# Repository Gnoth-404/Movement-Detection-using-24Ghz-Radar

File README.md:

# Movement-Detection-using-24Ghz-Radar
Adaptive movement detection using 24Ghz Radar and CFAR Algorithm

# Radar Movement Detection System

## Project Overview
This project implemented a radar-based movement detection system using  IPM165 radar sensor, FreeSoc2 Development Board, along with CA-CFAR algorithm. The system included custom PCB design, radar signal processing, and 3D-printed enclosure.

## Features
- 4-layer PCB design integrating IPM165 radar sensor
- Two-stage bandpass filter with gain of 300
- DMA streaming from ADC to Memory
- Signal processing using Hanning window and FFT
- Movement detection using CA-CFAR algorithm
- Custom 3D-printed enclosure

## Hardware
### PCB Design
- 4-layer PCB designed in Kicad
- Integrates IPM165 radar sensor
- Includes two-stage bandpass filter (Gain = 300)

### Enclosure
- Custom 3D-printed designed in Onshape

## Software
### Firmware (C)
- DMA streaming from ADC
- Hanning window application
- FFT implementation
- CA-CFAR algorithm for movement detection

### MATLAB
- Verification script for signal processing algorithms

## Results and Performance

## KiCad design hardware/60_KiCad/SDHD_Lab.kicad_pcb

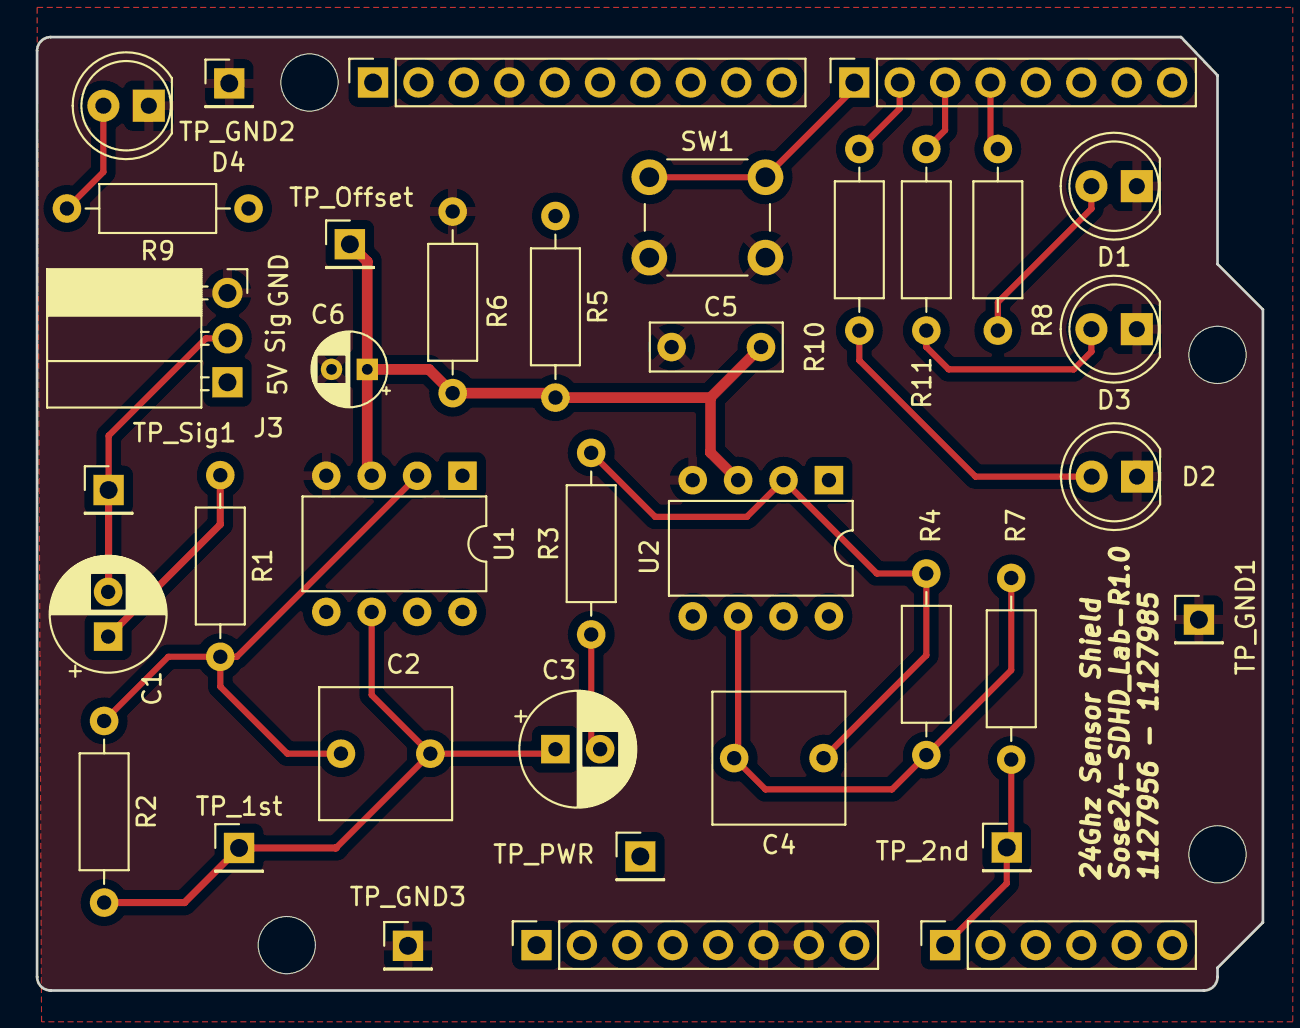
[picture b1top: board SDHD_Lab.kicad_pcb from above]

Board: 4 copper layers, 68.6 x 53.3 mm, 41 parts (0 on the bottom side), 19 nets.

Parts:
C1, C3: 4.7u; CP_Radial_D6.3mm_P2.50mm
C2: 1.5n; C_Rect_L7.2mm_W7.2mm_P5.00mm_FKS2_FKP2_MKS2_MKP2
C4: 3.3n; C_Rect_L7.2mm_W7.2mm_P5.00mm_FKS2_FKP2_MKS2_MKP2
C5: 100n; C_Rect_L7.2mm_W2.5mm_P5.00mm_FKS2_FKP2_MKS2_MKP2
C6: 22u; CP_Radial_D4.0mm_P2.00mm
D1: Red_LED; LED_D5.0mm
D2: Green_LED; LED_D5.0mm
D3: Yellow_LED; LED_D5.0mm
D4: Pwr_LED; LED_D5.0mm
J1: Power; PinSocket_1x08_P2.54mm_Vertical
J2: Analog; PinSocket_1x06_P2.54mm_Vertical
J3: Conn_01x03_Socket; PinSocket_1x03_P2.54mm_Horizontal
J4: Digital/PWM; PinSocket_1x10_P2.54mm_Vertical
J5: Digital/PWM; PinSocket_1x08_P2.54mm_Vertical
MH1, MH2, MH3, MH4: MountingHole_3.2mm
R1: 2.2k; R_Axial_DIN0207_L6.3mm_D2.5mm_P10.16mm_Horizontal
R2: 220k; R_Axial_DIN0207_L6.3mm_D2.5mm_P10.16mm_Horizontal
R3: 33k; R_Axial_DIN0207_L6.3mm_D2.5mm_P10.16mm_Horizontal
R4: 100k; R_Axial_DIN0207_L6.3mm_D2.5mm_P10.16mm_Horizontal
R5, R6: 1k; R_Axial_DIN0207_L6.3mm_D2.5mm_P10.16mm_Horizontal
R7: 100; R_Axial_DIN0207_L6.3mm_D2.5mm_P10.16mm_Horizontal
R8, R9, R10, R11: 470; R_Axial_DIN0207_L6.3mm_D2.5mm_P10.16mm_Horizontal
SW1: SW_Push; SW_PUSH_6mm_H7.3mm
TP_1st: TP_1st; PinHeader_1x01_P2.54mm_Vertical
TP_2nd: TP_2nd; PinHeader_1x01_P2.54mm_Vertical
TP_GND1, TP_GND2, TP_GND3: TestPoint; PinHeader_1x01_P2.54mm_Vertical
TP_Offset: TP_Offset; PinHeader_1x01_P2.54mm_Vertical
TP_PWR: TP_5V; PinHeader_1x01_P2.54mm_Vertical
TP_Sig1: TP_Sig; PinHeader_1x01_P2.54mm_Vertical
U1, U2: OPA340P; DIP-8_W7.62mm

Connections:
+5V: J1.5, J3.1, R5.1, R9.1, TP_PWR.1, U1.7 (V+), U2.7 (V+)
/LED_GREEN: J5.2, R10.1
/LED_RED: J5.4, R8.1
/LED_YELLOW: J5.3, R11.1
/Radar_Sig: C1.2, J3.2, TP_Sig1.1
/SW_BUTTON: J5.1, SW1.1
/V_offset: C5.1, C6.1, R5.2, R6.1, TP_Offset.1, U1.3 (+), U2.3 (+)
/V_out: J2.1, R7.2, TP_2nd.1
GND: C5.2, C6.2, D1.1 (K), D2.1 (K), D3.1 (K), D4.1 (K), J1.6, J1.7, J3.3, J4.4, R6.2, SW1.2, TP_GND1.1, TP_GND2.1, TP_GND3.1, U1.4 (V-), U2.4 (V-)
unnamed: C1.1, R1.1
unnamed: C2.2, C3.1, R2.2, TP_1st.1, U1.6
unnamed: C3.2, R3.1
unnamed: C4.2, R4.2, R7.1, U2.6
unnamed: D1.2 (A), R8.2
unnamed: D2.2 (A), R10.2
unnamed: D3.2 (A), R11.2
unnamed: D4.2 (A), R9.2
unnamed: C2.1, R1.2, R2.1, U1.2 (-)
unnamed: C4.1, R3.2, R4.1, U2.2 (-)

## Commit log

2024-10-03 Uploaded firmware
    - 3 Projects
    - Sending ADC Data to Matlab
    - Sending FFT Data to Matlab
    - CFAR Algorithm in C
2024-10-03 Uploaded documentation
2024-10-03 Matlab script
2024-10-03 Uploaded Hardware desciption
    - Simulation
    - Kicad Project
    - Gerber file
2024-10-03 Uploaded 3D printed file
2024-10-03 Uploaded presentation file
2024-10-04 Added Description
2024-10-04 Fixed syntax error
2024-10-15 Upload PCB image
2024-10-15 Add pcb image to wiki
